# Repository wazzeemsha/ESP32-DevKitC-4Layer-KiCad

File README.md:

# ESP32 DevKitC 4-Layer PCB Design

## Overview
This project is a custom 4-layer PCB design based on the ESP32 DevKitC module, designed using KiCad 10. It demonstrates multilayer PCB design, schematic capture, PCB layout, component placement, routing, and generation of manufacturing-ready files.

## Features
- ESP32 DevKitC-based design
- 4-layer PCB stack-up
- USB Micro-B interface
- Ground and power planes
- Through-hole and SMD components
- Manufacturing-ready Gerber files

## Software Used
- KiCad 10
- Git
- GitHub

## Repository Structure
```
├── Images/
│   ├── PCB_Layout.png
│   ├── PCB_Schematic.png
│   ├── PCB_3D_Top.png
│   └── PCB_3D_Bottom.png
│
├── Gerber_Files/
│   ├── *.gbr
│   ├── *.drl
│   └── *.gbrjob
│
├── *.kicad_pro
├── *.kicad_sch
├── *.kicad_pcb
└── README.md
```

## Design Verification
- ✔ Electrical Rules Check (ERC) completed
- ✔ Design Rules Check (DRC) completed
- ✔ Gerber and drill files generated successfully

## Images
The `Images` folder contains:
- PCB Layout
- PCB Schematic
- 3D Top View
- 3D Bottom View

## Gerber Files
The `Gerber_Files` folder contains all files required for PCB fabrication.

## License
This project is shared for educational and portfolio purposes.

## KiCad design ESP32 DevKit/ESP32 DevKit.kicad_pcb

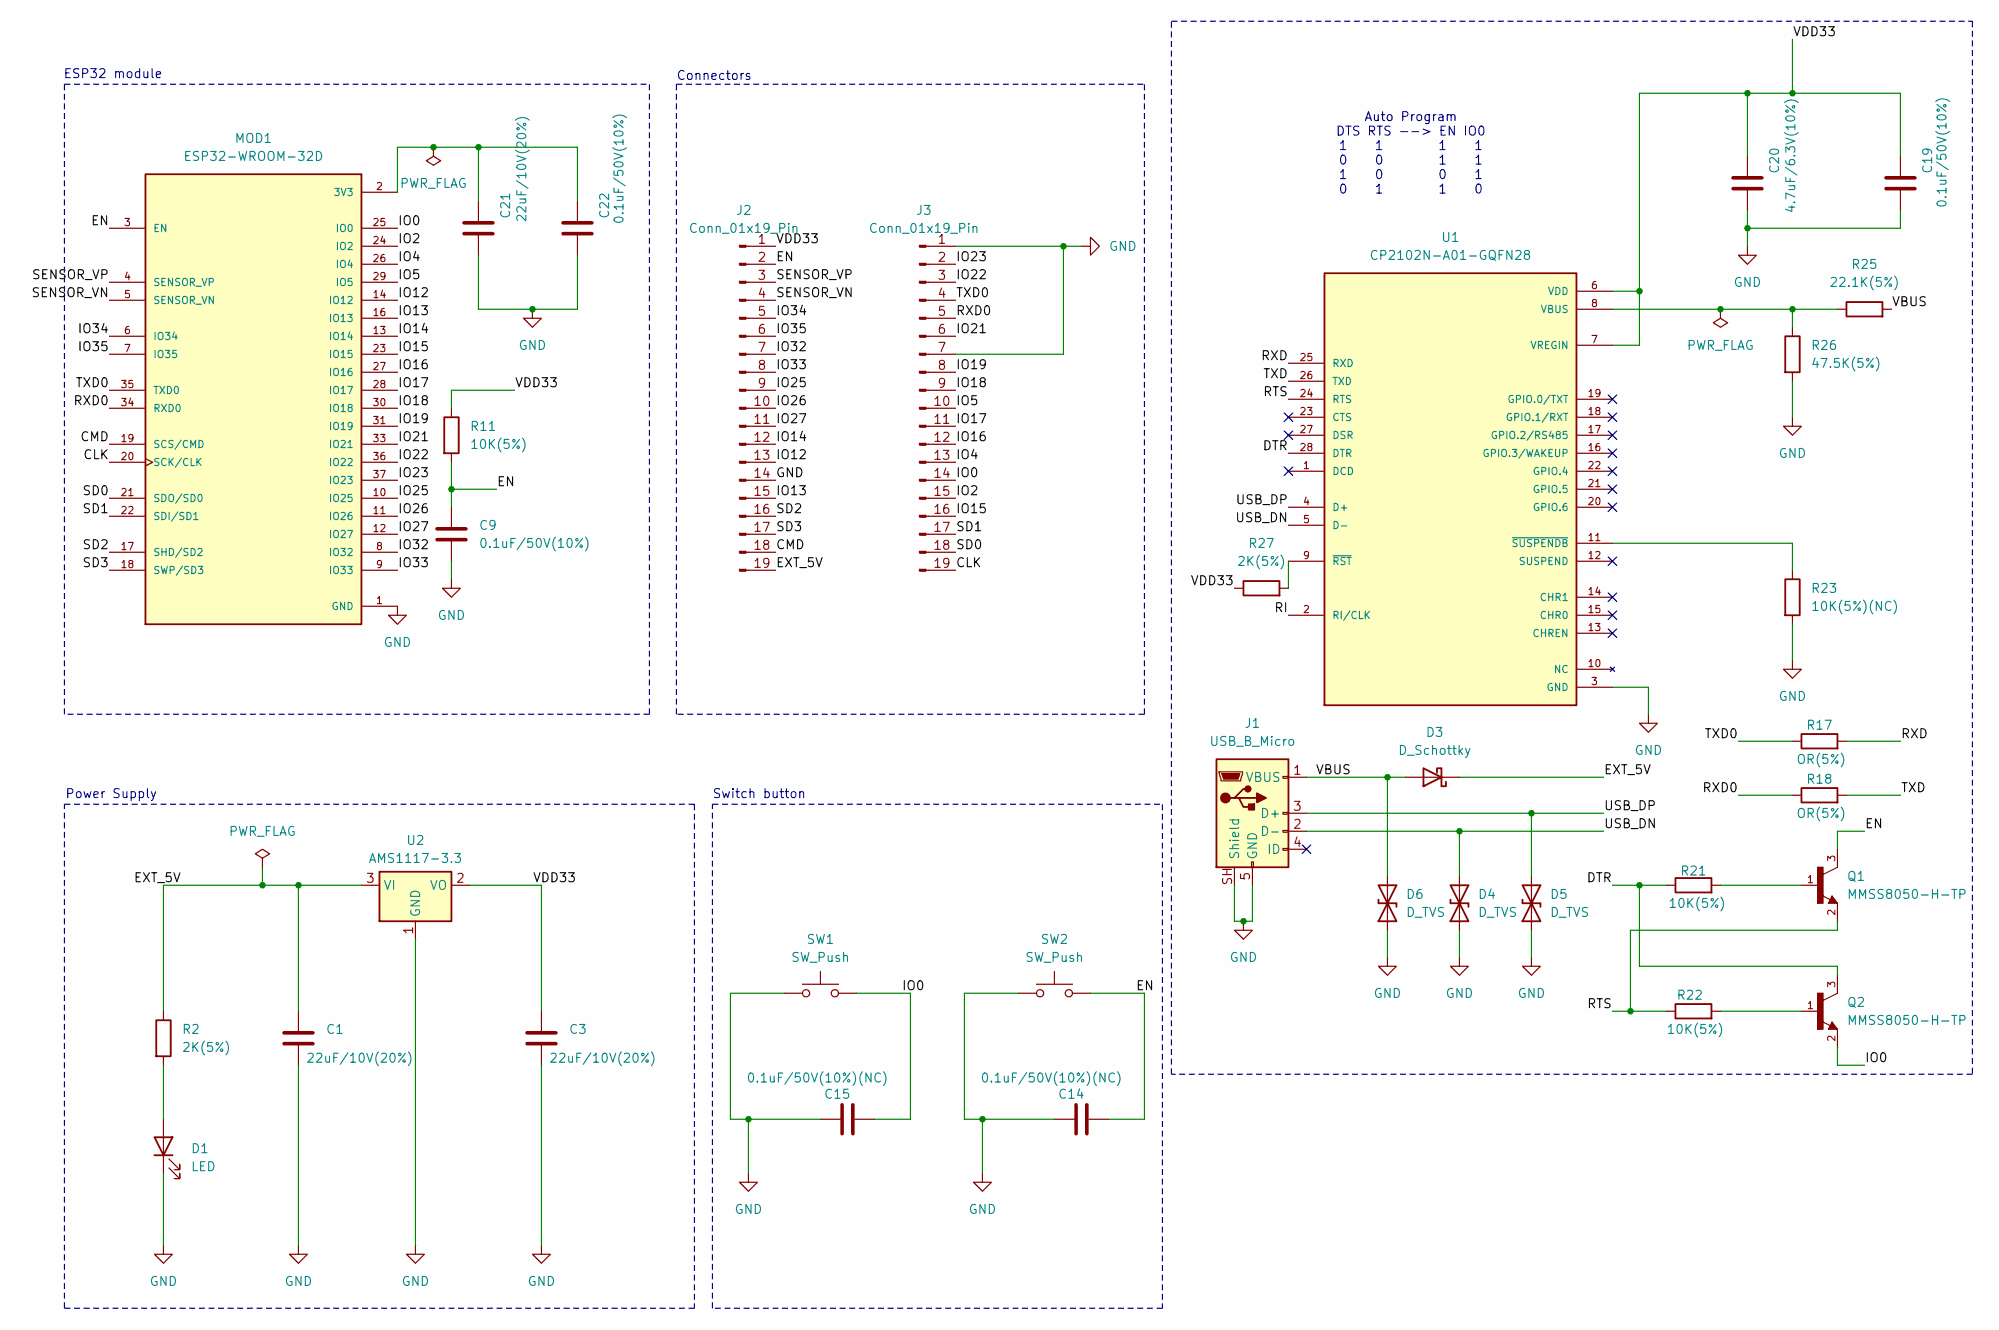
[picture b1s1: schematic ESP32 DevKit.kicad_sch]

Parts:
C1, C3, C21: 22uF/10V(20%); C_0805_2012Metric
C9, C19, C22: 0.1uF/50V(10%); C_0603_1608Metric
C14, C15: 0.1uF/50V(10%)(NC); C_0603_1608Metric
C20: 4.7uF/6.3V(10%); C_0805_2012Metric
D1: LED; LED_0603_1608Metric
D3: D_Schottky; D_SOD-323
D4, D5, D6: D_TVS; D_SOD-523
J1: USB_B_Micro; USB_Micro-B_GCT_USB3076-30-A
J2, J3: Conn_01x19_Pin; PinHeader_1x19_P2.54mm_Vertical
MOD1: ESP32-WROOM-32D; MODULE_ESP32-WROOM-32D; PARTREV 1.9
Q1, Q2: MMSS8050-H-TP; PARTREV D
R2, R27: 2K(5%); R_0603_1608Metric
R11, R21, R22: 10K(5%); R_0603_1608Metric
R17, R18: OR(5%); R_0603_1608Metric
R23: 10K(5%)(NC); R_0603_1608Metric
R25: 22.1K(5%); R_0603_1608Metric
R26: 47.5K(5%); R_0603_1608Metric
SW1, SW2: SW_Push; SW_SPST_B3S-1000
U1: CP2102N-A01-GQFN28; CP2102N; PARTREV 1.0
U2: AMS1117-3.3; SOT-223-3_TabPin2

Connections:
/CLK: J3.19, MOD1.20 (SCK/CLK)
/CMD: J2.18, MOD1.19 (SCS/CMD)
/DTR: Q2.3, R21.1, U1.28 (DTR)
/EN: C9.1, C14.2, J2.2, MOD1.3 (EN), Q1.3, R11.2, SW2.2
/EXT_5V: C1.1, D3.1 (K), J2.19, R2.1, U2.3 (VI)
/IO0: C15.2, J3.14, MOD1.25 (IO0), Q2.2, SW1.2
/IO2: J3.15, MOD1.24 (IO2)
/IO4: J3.13, MOD1.26 (IO4)
/IO5: J3.10, MOD1.29 (IO5)
/IO12: J2.13, MOD1.14 (IO12)
/IO13: J2.15, MOD1.16 (IO13)
/IO14: J2.12, MOD1.13 (IO14)
/IO15: J3.16, MOD1.23 (IO15)
/IO16: J3.12, MOD1.27 (IO16)
/IO17: J3.11, MOD1.28 (IO17)
/IO18: J3.9, MOD1.30 (IO18)
/IO19: J3.8, MOD1.31 (IO19)
/IO21: J3.6, MOD1.33 (IO21)
/IO22: J3.3, MOD1.36 (IO22)
/IO23: J3.2, MOD1.37 (IO23)
/IO25: J2.9, MOD1.10 (IO25)
/IO26: J2.10, MOD1.11 (IO26)
/IO27: J2.11, MOD1.12 (IO27)
/IO32: J2.7, MOD1.8 (IO32)
/IO33: J2.8, MOD1.9 (IO33)
/IO34: J2.5, MOD1.6 (IO34)
/IO35: J2.6, MOD1.7 (IO35)
/RI: U1.2 (RI/CLK)
/RTS: Q1.2, R22.1, U1.24 (RTS)
/RXD: R17.2, U1.25 (RXD)
/RXD0: J3.5, MOD1.34 (RXD0), R18.1
/SD0: J3.18, MOD1.21 (SDO/SD0)
/SD1: J3.17, MOD1.22 (SDI/SD1)
/SD2: J2.16, MOD1.17 (SHD/SD2)
/SD3: J2.17, MOD1.18 (SWP/SD3)
/SENSOR_VN: J2.4, MOD1.5 (SENSOR_VN)
/SENSOR_VP: J2.3, MOD1.4 (SENSOR_VP)
/TXD: R18.2, U1.26 (TXD)
/TXD0: J3.4, MOD1.35 (TXD0), R17.1
/USB_DN: D4.2 (A2), J1.2 (D-), U1.5 (D-)
/USB_DP: D5.2 (A2), J1.3 (D+), U1.4 (D+)
/VBUS: D3.2 (A), D6.2 (A2), J1.1 (VBUS), R25.2
/VDD33: C3.1, C19.1, C20.1, J2.1, R11.1, R27.1, U1.6 (VDD), U1.7 (VREGIN), U2.2 (VO)
GND: C1.2, C3.2, C9.2, C14.1, C15.1, C19.2, C20.2, C21.2, C22.2, D1.1 (K), D4.1 (A1), D5.1 (A1), D6.1 (A1), J1.5 (GND), J1.SH (Shield), J2.14, J3.1, J3.7, MOD1.1 (GND), MOD1.15 (GND), MOD1.38 (GND), MOD1.39_1 (GND), MOD1.39_2 (GND), MOD1.39_3 (GND), MOD1.39_4 (GND), MOD1.39_5 (GND), MOD1.39_6 (GND), MOD1.39_7 (GND), MOD1.39_8 (GND), MOD1.39_9 (GND), MOD1.39_10 (GND), MOD1.39_11 (GND), MOD1.39_12 (GND), MOD1.39_13 (GND), MOD1.39_14 (GND), MOD1.39_15 (GND), MOD1.39_16 (GND), MOD1.39_17 (GND), MOD1.39_18 (GND), MOD1.39_19 (GND), MOD1.39_20 (GND), MOD1.39_21 (GND), R23.2, R26.2, SW1.1, SW2.1, U1.3 (GND), U1.29 (GND), U2.1 (GND)
unnamed: D1.2 (A), R2.2
unnamed: C21.1, C22.1, MOD1.2 (3V3)
unnamed: Q1.1, R21.2
unnamed: Q2.1, R22.2
unnamed: R25.1, R26.1, U1.8 (VBUS)
unnamed: R27.2, U1.9 (~RST)
unnamed: R23.1, U1.11 (~SUSPENDB)

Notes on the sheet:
Auto Program DTS RTS --> EN IO0 1 1 1 1 0 0 1 1 1 0 0 1 0 1 1 0
Switch button
Power Supply
Connectors
ESP32 module

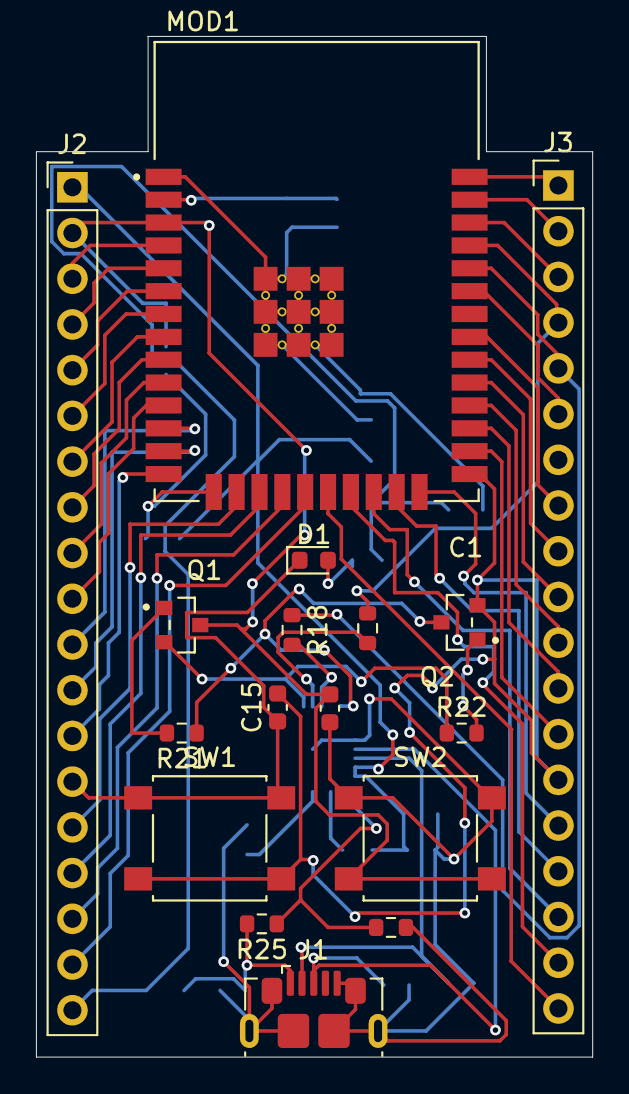
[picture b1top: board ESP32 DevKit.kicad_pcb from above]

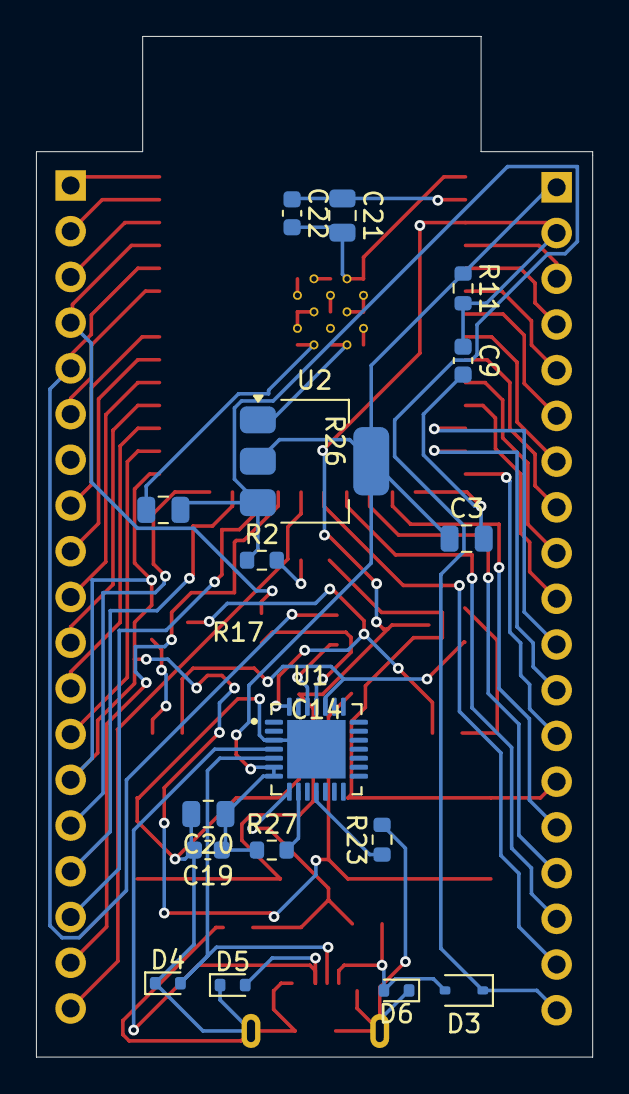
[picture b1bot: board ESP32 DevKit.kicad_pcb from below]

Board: 4 copper layers, 30.9 x 56.7 mm, 34 parts (17 on the bottom side), 50 nets.

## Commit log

2026-06-28 Finished Work
2026-06-28 Create Gerber_Files folder with description
    Add description for Gerber and Drill files folder
2026-06-28 Add Gerber files
2026-06-28 Images added
